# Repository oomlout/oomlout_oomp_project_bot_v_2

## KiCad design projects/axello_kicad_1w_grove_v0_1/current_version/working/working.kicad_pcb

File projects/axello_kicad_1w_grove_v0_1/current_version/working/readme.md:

# kicad
 
## summary 
* id: axello_kicad_1w_grove_v0_1
* user: axello
* name: kicad
* board: 1w_grove_v0_1
* repo: https://github.com/axello/kicad
* src_file_repo_kicad_pcb: 6.0/projects/1w-grove-v0.1/1w-grove-v0.1.kicad_pcb
* src_file_repo_kicad_pcb_link: https://github.com/axello/kicad/tree/master/6.0/projects/1w-grove-v0.1/1w-grove-v0.1.kicad_pcb
* src_file_repo_kicad_sch: 6.0/projects/1w-grove-v0.1/1w-grove-v0.1.kicad_sch
* src_file_repo_kicad_sch_link: https://github.com/axello/kicad/tree/master/6.0/projects/1w-grove-v0.1/1w-grove-v0.1.kicad_sch

* src_file_repo_sch: 6.0/projects/1w-grove-v0.1/1w-grove-v0.1.sch
* src_file_repo_sch_link: https://github.com/axello/kicad/tree/master/6.0/projects/1w-grove-v0.1/1w-grove-v0.1.sch
* full details link: https://github.com/oomlout/oomlout_oomp_project_bot_v_2/tree/main/projects/axello_kicad_1w_grove_v0_1/current_version/working  

## pcb  

[board (pdf)](working.pdf)  

## working_bom
| Id | Designator | Footprint | Quantity | Designation | Supplier and ref |  | None | 
| --- | --- | --- | --- | --- | --- | --- | --- | 
| 1 | U4,U6,U10,U11 | schroef_3.5mm | 4 | schroef_3.5mm |  |  | [''] | 
| 2 | C1 | C_0805_2012Metric | 1 | 100pF |  |  | [''] | 
| 3 | C2 | C_0805_2012Metric | 1 | 100nF |  |  | [''] | 
| 4 | Q1 | SOT-323 | 1 | BSS138BKW |  |  | [''] | 
| 5 | Q2 | SOT-23-3 | 1 | NX2301P |  |  | [''] | 
| 6 | R1,R2,R7 | R_0805_2012Metric | 3 | 10k |  |  | [''] | 
| 7 | R4 | R_0805_2012Metric | 1 | 5.6k |  |  | [''] | 
| 8 | R5,R6,R8 | R_0805_2012Metric | 3 | 22R |  |  | [''] | 
| 9 | CN2,CN3,CN4,CN1,CN5 | rj10-v2 | 5 | RJ10 |  |  | [''] | 
| 10 | F1 | C1210 | 1 | Polyfuse_Small |  |  | [''] | 
| 11 | CN6 | grove-v0.1 | 1 | grove |  |  | [''] | 
| 12 | U3 | CE-140 | 1 | CE-mark |  |  | [''] |

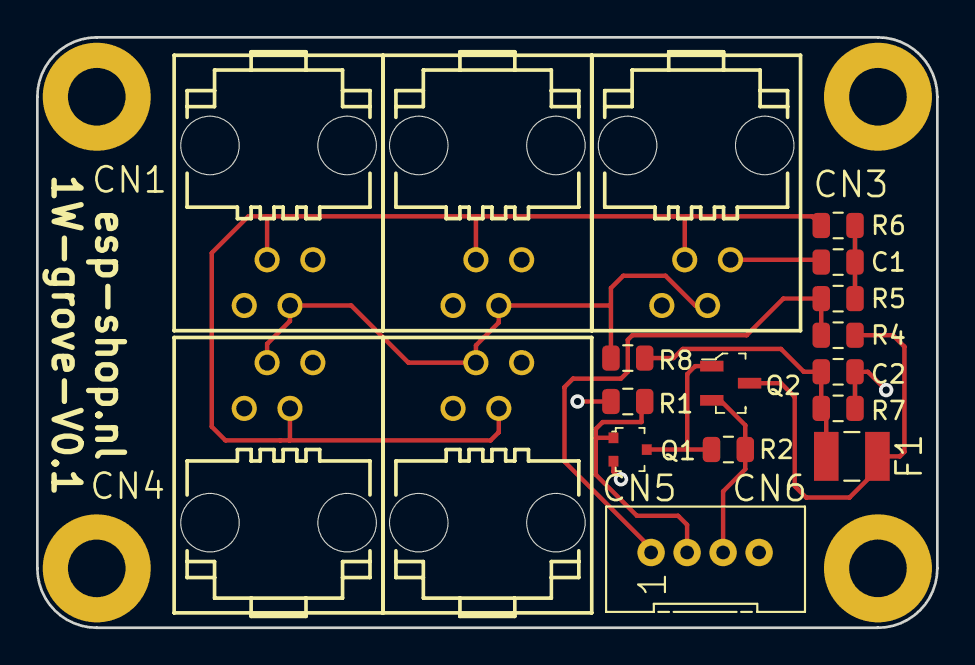
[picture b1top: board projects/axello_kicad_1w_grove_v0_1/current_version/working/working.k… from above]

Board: 2 copper layers, 50.0 x 32.8 mm, 23 parts (1 on the bottom side), 10 nets.

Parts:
C1: 100pF; C_0805_2012Metric
C2: 100nF; C_0805_2012Metric
CN1, CN2, CN3, CN4, CN5: RJ10; rj10-v2
CN6: grove; grove-v0.1
F1: Polyfuse_Small; C1210
Q1: BSS138BKW; SOT-323
Q2: NX2301P; SOT-23-3
R1, R2, R7: 10k; R_0805_2012Metric
R4: 5.6k; R_0805_2012Metric
R5, R6, R8: 22R; R_0805_2012Metric
U3: CE-mark; CE-140
U4, U6, U10, U11: schroef_3.5mm

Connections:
unnamed: C1.1, R5.2, R6.1
unnamed: C1.2, C2.2, CN1.1, CN2.1, CN3.1, CN4.1, CN5.1, CN6.4, Q1.2 (S), R1.1, R7.1
unnamed: C2.1, F1.1, R7.2, R8.1
unnamed: CN1.2, CN2.2, CN3.2, CN4.2, CN5.2, R8.2
unnamed: CN1.3, CN2.3, CN3.3, CN4.3, CN5.3, R6.2
unnamed: F1.2, Q2.3 (D), R4.2
unnamed: CN6.2, Q1.1 (G), R1.2
unnamed: Q1.3 (D), Q2.1 (G), R2.1
unnamed: CN6.3, Q2.2 (S), R2.2
unnamed: CN6.1, R4.1, R5.1

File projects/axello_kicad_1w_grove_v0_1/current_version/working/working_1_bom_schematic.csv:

"Source:","C:\gh\oomlout_oomp_project_bot_v_2\projects\axello_kicad_1w_grove_v0_1\current_version\working\working_1.kicad_sch"
"Date:","26/09/2023 20:39:30"
"Tool:","Eeschema 7.0.6"
"Generator:","C:/Program Files/KiCad/7.0/bin/scripting/plugins/bom_csv_grouped_by_value_with_fp.py"
"Component Count:","26"
"Ref","Qnty","Value","Cmp name","Footprint","Description","Vendor","DNP"
"C1","1","100pF","Device_C","1wire-v0.4:C_0805_2012Metric","","",""
"C2","1","100nF","Device_C","1wire-v0.4:C_0805_2012Metric","","",""
"CN1, CN2, CN3, CN4, CN5","5","RJ10","RJ10","1w-esp32-v0.4:rj10-v2","","",""
"CN6","1","grove","RJ10","grove:grove-v0.1","","",""
"F1","1","Polyfuse_Small","Polyfuse_Small","1wire-v0.4:C1210","","",""
"FID1, FID2, FID3","3","Fiducial","Fiducial","1w-esp32-v0.4:Fiducial_1mm_Mask3mm","","",""
"Q1","1","BSS138BKW","Device_Q_NMOS_GSD","1wire-v0.4:SOT-323","","",""
"Q2","1","NX2301P","Device_Q_PMOS_GSD","1wire-v0.4:SOT-23-3","","",""
"R1, R2, R7","3","10k","Device_R_Small","1wire-v0.4:R_0805_2012Metric","","",""
"R4","1","5.6k","Device_R_Small","1wire-v0.4:R_0805_2012Metric","","",""
"R5, R6, R8","3","22R","Device_R_Small","1wire-v0.4:R_0805_2012Metric","","",""
"U3","1","CE-mark","CE-mark","1w-esp32-v0.4:CE-140","","",""
"U4, U6, U10, U11","4","schroef_3.5mm","schroef_3.5mm","1w-esp32-v0.4:schroef_3.5mm","","",""

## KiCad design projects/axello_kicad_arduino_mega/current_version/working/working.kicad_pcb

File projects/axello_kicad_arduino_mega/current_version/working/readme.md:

# kicad
 
## summary 
* id: axello_kicad_arduino_mega
* user: axello
* name: kicad
* board: arduino_mega
* repo: https://github.com/axello/kicad
* src_file_repo_kicad_pcb: Arduino_Mega_433Mhz_Shield/Arduino_Mega.kicad_pcb
* src_file_repo_kicad_pcb_link: https://github.com/axello/kicad/tree/master/Arduino_Mega_433Mhz_Shield/Arduino_Mega.kicad_pcb
* src_file_repo_kicad_sch: 6.0/projects/NodeMCU-Metriful2/NodeMCU-Metriful.kicad_sch
* src_file_repo_kicad_sch_link: https://github.com/axello/kicad/tree/master/6.0/projects/NodeMCU-Metriful2/NodeMCU-Metriful.kicad_sch

* src_file_repo_sch: Arduino_Mega_433Mhz_Shield/Arduino_Mega.sch
* src_file_repo_sch_link: https://github.com/axello/kicad/tree/master/Arduino_Mega_433Mhz_Shield/Arduino_Mega.sch
* full details link: https://github.com/oomlout/oomlout_oomp_project_bot_v_2/tree/main/projects/axello_kicad_arduino_mega/current_version/working  

## schematic  
  
[schematic (pdf)](working_schematic.pdf) 

## pcb  

[board (pdf)](working.pdf)  

## working_bom
| Id | Designator | Footprint | Quantity | Designation | Supplier and ref |  | None | 
| --- | --- | --- | --- | --- | --- | --- | --- | 
| 1 | P9,P10,P13 | Arduino_1pin | 3 | CONN_01X01 |  |  | [''] | 
| 2 | J1 | Power_Strip_Arduino_Mega_2x18 | 1 | Arduino Mega POWER |  |  | [''] | 
| 3 | P1 | Socket_Strip_Arduino_1x08 | 1 | Communication |  |  | [''] | 
| 4 | AE1 | Pin_Header_Straight_1x01 | 1 | Tx Antenna |  |  | [''] | 
| 5 | AE2 | Pin_Header_Straight_1x01 | 1 | Rx Antenna |  |  | [''] | 
| 6 | U1 | RCV | 1 | RXB6_RCV |  |  | [''] | 
| 7 | U2 | XMIT | 1 | RXB6_XMIT |  |  | [''] | 
| 8 | C1 | C_Rect_L9.0mm_W2.5mm_P7.50mm_MKT | 1 | 100n |  |  | [''] | 
| 9 | C2 | CP_Radial_D5.0mm_P2.00mm | 1 | 0.47Âµ |  |  | [''] | 
| 10 | C3 | CP_Radial_D5.0mm_P2.00mm | 1 | 10ÂµF |  |  | [''] | 
| 11 | JP1 | Pin_Header_Straight_1x02_Pitch1.27mm | 1 | RF_GND |  |  | [''] | 
| 12 | G*** | LOGO2 | 1 | LOGO |  |  | [''] | 

## bom_schematic
| Ref | Qnty | Value | Cmp name | Footprint | Description | Vendor | DNP | 
| --- | --- | --- | --- | --- | --- | --- | --- | 
| AE1, AE2 | 2 | Antenna | Antenna | Pin_Headers:Pin_Header_Straight_1x01 |  |  |  | 
| C1 | 1 | 100n | C_Small | Capacitors_THT:C_Rect_L9.0mm_W2.5mm_P7.50mm_MKT |  |  |  | 
| C2 | 1 | 0.47Âµ | CP | Capacitors_THT:CP_Radial_D5.0mm_P2.00mm |  |  |  | 
| C3 | 1 | 10ÂµF | CP | Capacitors_THT:CP_Radial_D5.0mm_P2.00mm |  |  |  | 
| J1 | 1 | Arduino_Mega_POWER | ARDUINO_MEGA_POWER | Socket_Arduino_Mega:Power_Strip_Arduino_Mega_2x18 |  |  |  | 
| JP1 | 1 | RF_GND | Jumper_NO_Small | Pin_Headers:Pin_Header_Straight_1x02_Pitch1.27mm |  |  |  | 
| P1 | 1 | Communication | CONN_01X08 | Socket_Arduino_Mega:Socket_Strip_Arduino_1x08 |  |  |  | 
| U1 | 1 | RXB6_RCV | RXB6_RCV | RF:RCV |  |  |  | 
| U2 | 1 | RXB6_XMIT | RXB6_XMIT | RF:XMIT |  |  |  |

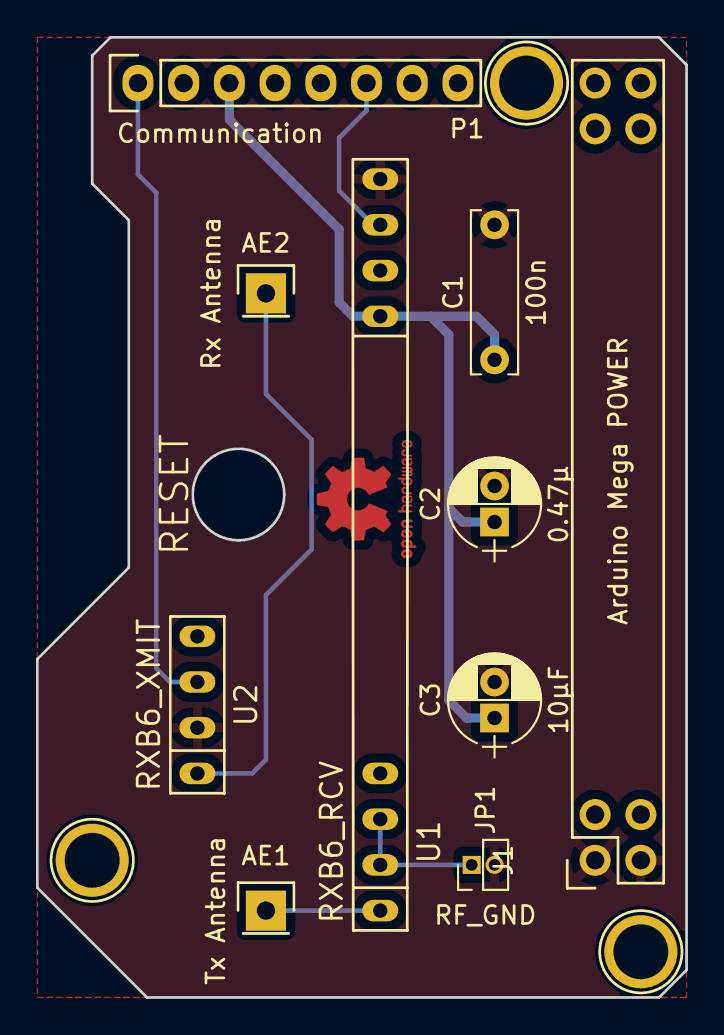
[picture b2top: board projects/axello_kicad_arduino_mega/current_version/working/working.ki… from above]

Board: 2 copper layers, 36.1 x 53.3 mm, 13 parts (0 on the bottom side), 8 nets.

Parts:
AE1: Tx Antenna; Pin_Header_Straight_1x01
AE2: Rx Antenna; Pin_Header_Straight_1x01
C1: 100n; C_Rect_L9.0mm_W2.5mm_P7.50mm_MKT
C2: 0.47µ; CP_Radial_D5.0mm_P2.00mm
C3: 10µF; CP_Radial_D5.0mm_P2.00mm
J1: Arduino Mega POWER; Power_Strip_Arduino_Mega_2x18
JP1: RF_GND; Pin_Header_Straight_1x02_Pitch1.27mm
P1: Communication; Socket_Strip_Arduino_1x08
P9, P10, P13: CONN_01X01; Arduino_1pin
U1: RXB6_RCV; RCV
U2: RXB6_XMIT; XMIT

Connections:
+5V: J1.35, J1.36, U2.4
/14(Tx3): P1.1, U2.3
/16(Tx2): C1.1, C2.1, C3.1, P1.3, U1.5
/19(Rx1): P1.6, U1.7
GND: C1.2, C2.2, C3.2, J1.1, J1.2, JP1.2, U1.8, U2.2
unnamed: AE1.1, U1.1
unnamed: AE2.1, U2.1
unnamed: JP1.1, U1.2, U1.3

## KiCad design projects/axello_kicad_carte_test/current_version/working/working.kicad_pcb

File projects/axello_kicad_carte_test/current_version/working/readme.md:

# kicad
 
## summary 
* id: axello_kicad_carte_test
* user: axello
* name: kicad
* board: carte_test
* repo: https://github.com/axello/kicad
* src_file_repo_kicad_pcb: demos/test_xil_95108/carte_test.kicad_pcb
* src_file_repo_kicad_pcb_link: https://github.com/axello/kicad/tree/master/demos/test_xil_95108/carte_test.kicad_pcb
* src_file_repo_kicad_sch: demos/test_xil_95108/carte_test.kicad_sch
* src_file_repo_kicad_sch_link: https://github.com/axello/kicad/tree/master/demos/test_xil_95108/carte_test.kicad_sch

* src_file_repo_sch: Arduino_Mega_433Mhz_Shield/Arduino_Mega.sch
* src_file_repo_sch_link: https://github.com/axello/kicad/tree/master/Arduino_Mega_433Mhz_Shield/Arduino_Mega.sch
* full details link: https://github.com/oomlout/oomlout_oomp_project_bot_v_2/tree/main/projects/axello_kicad_carte_test/current_version/working  

## schematic  
  
[schematic (pdf)](working_schematic.pdf) 

## pcb  

[board (pdf)](working.pdf)  

## working_bom
| Id | Designator | Footprint | Quantity | Designation | Supplier and ref |  | None | 
| --- | --- | --- | --- | --- | --- | --- | --- | 
| 1 | D1,D4 | D_DO-35_SOD27_P12.70mm_Horizontal | 2 | 1N4004 |  |  | [''] | 
| 2 | SW1,SW2 | SW_PUSH_6mm_h4.3mm | 2 | SW_PUSH |  |  | [''] | 
| 3 | U2 | PLCC84 | 1 | XC95108PC84 |  |  | [''] | 
| 4 | U4 | DIP-14_W7.62mm_LongPads | 1 | 74HC04 |  |  | [''] | 
| 5 | P4 | PinHeader_2x02_P2.54mm_Vertical | 1 | CONN_2X2 |  |  | [''] | 
| 6 | K1 | PinHeader_1x03_P2.54mm_Vertical | 1 | CONN_3 |  |  | [''] | 
| 7 | R2,R3 | R_Axial_DIN0207_L6.3mm_D2.5mm_P10.16mm_Horizontal | 2 | 330 |  |  | [''] | 
| 8 | R8,R9 | R_Axial_DIN0207_L6.3mm_D2.5mm_P10.16mm_Horizontal | 2 | 2,2K |  |  | [''] | 
| 9 | R10 | R_Axial_DIN0207_L6.3mm_D2.5mm_P10.16mm_Horizontal | 1 | 75 |  |  | [''] | 
| 10 | R1 | R_Axial_DIN0207_L6.3mm_D2.5mm_P10.16mm_Horizontal | 1 | 100K |  |  | [''] | 
| 11 | R5,R4 | R_Axial_DIN0207_L6.3mm_D2.5mm_P10.16mm_Horizontal | 2 | 4,7K |  |  | [''] | 
| 12 | R6 | R_Axial_DIN0207_L6.3mm_D2.5mm_P10.16mm_Horizontal | 1 | 1,1k |  |  | [''] | 
| 13 | U1 | DIP-16_W7.62mm_Socket_LongPads | 1 | TDA8702 |  |  | [''] | 
| 14 | X1 | Crystal_HC18-U_Horizontal | 1 | 10MHz |  |  | [''] | 
| 15 | R7 | R_Axial_DIN0207_L6.3mm_D2.5mm_P10.16mm_Horizontal | 1 | 1,1K |  |  | [''] | 
| 16 | D3,D2 | LED_D5.0mm | 2 | LED |  |  | [''] | 
| 17 | U6 | DIP-8_W7.62mm_LongPads | 1 | LM318N |  |  | [''] | 
| 18 | J1 | DSUB-25_Female_Horizontal_P2.77x2.84mm_EdgePinOffset9.90mm_Housed_MountingHolesOffset11.32mm | 1 | DB25 |  |  | [''] | 
| 19 | U3 | TO-220-3_Horizontal_TabDown | 1 | LM7805 |  |  | [''] | 
| 20 | J2 | DSUB-9_Female_Horizontal_P2.77x2.84mm_EdgePinOffset4.94mm_Housed_MountingHolesOffset7.48mm | 1 | DB9FEM |  |  | [''] | 
| 21 | P2 | TerminalBlock_Phoenix_MKDS-1,5-3-5.08_1x03_P5.08mm_Horizontal | 1 | CONN_3 |  |  | [''] | 
| 22 | P3 | TerminalBlock_Phoenix_MKDS-1,5-2-5.08_1x02_P5.08mm_Horizontal | 1 | CONN_2 |  |  | [''] | 
| 23 | C13,C3,C2,C14 | CP_Axial_L10.0mm_D4.5mm_P15.00mm_Horizontal | 4 | 10uF |  |  | [''] | 
| 24 | C6 | CP_Axial_L10.0mm_D4.5mm_P15.00mm_Horizontal | 1 | 47uF |  |  | [''] | 
| 25 | U5 | DIP-28__300__600_ELL | 1 | RAM_32KO |  |  | [''] | 
| 26 | C1,C12 | C_1206 | 2 | 100nF |  |  | [''] | 
| 27 | C4,C5 | C_1206 | 2 | 22pF |  |  | [''] | 
| 28 | C11,C10,C8,C7 | C_1206_3216Metric_Pad1.24x1.80mm_HandSolder | 4 | 100nF |  |  | [''] | 

## bom_schematic
| Ref | Qnty | Value | Cmp name | Footprint | Description | Vendor | DNP | 
| --- | --- | --- | --- | --- | --- | --- | --- | 
| C1, C12 | 2 | 100nF | C | Capacitors_SMD:C_1206 | Unpolarized capacitor |  |  | 
| C2, C3, C13, C14 | 4 | 10uF | CP | Capacitor_THT:CP_Axial_L10.0mm_D4.5mm_P15.00mm_Horizontal | Polarised capacitor |  |  | 
| C4, C5 | 2 | 22pF | C | Capacitors_SMD:C_1206 | Unpolarized capacitor |  |  | 
| C6 | 1 | 47uF | CP | Capacitor_THT:CP_Axial_L10.0mm_D4.5mm_P15.00mm_Horizontal | Polarised capacitor |  |  | 
| C7, C8, C10, C11 | 4 | 100nF | C | Capacitor_SMD:C_1206_3216Metric_Pad1.24x1.80mm_HandSolder | Unpolarized capacitor |  |  | 
| D1, D4 | 2 | 1N4004 | DIODE | Diode_THT:D_DO-35_SOD27_P12.70mm_Horizontal |  |  |  | 
| D2, D3 | 2 | LED | LED | LED_THT:LED_D5.0mm |  |  |  | 
| J1 | 1 | DB25 | DB25 | Connector_Dsub:DSUB-25_Female_Horizontal_P2.77x2.84mm_EdgePinOffset9.90mm_Housed_MountingHolesOffset11.32mm |  |  |  | 
| J2 | 1 | DB9FEM | DB9 | Connector_Dsub:DSUB-9_Female_Horizontal_P2.77x2.84mm_EdgePinOffset4.94mm_Housed_MountingHolesOffset7.48mm |  |  |  | 
| K1 | 1 | CONN_3 | CONN_3 | Connector_PinHeader_2.54mm:PinHeader_1x03_P2.54mm_Vertical |  |  |  | 
| P2 | 1 | CONN_3 | CONN_3 | TerminalBlock_Phoenix:TerminalBlock_Phoenix_MKDS-1,5-3-5.08_1x03_P5.08mm_Horizontal |  |  |  | 
| P3 | 1 | CONN_2 | CONN_2 | TerminalBlock_Phoenix:TerminalBlock_Phoenix_MKDS-1,5-2-5.08_1x02_P5.08mm_Horizontal |  |  |  | 
| P4 | 1 | CONN_2X2 | CONN_2X2 | Connector_PinHeader_2.54mm:PinHeader_2x02_P2.54mm_Vertical |  |  |  | 
| R1 | 1 | 100K | R | Resistor_THT:R_Axial_DIN0207_L6.3mm_D2.5mm_P10.16mm_Horizontal | Resistor |  |  | 
| R2, R3 | 2 | 330 | R | Resistor_THT:R_Axial_DIN0207_L6.3mm_D2.5mm_P10.16mm_Horizontal | Resistor |  |  | 
| R4, R5 | 2 | 4,7K | R | Resistor_THT:R_Axial_DIN0207_L6.3mm_D2.5mm_P10.16mm_Horizontal | Resistor |  |  | 
| R6 | 1 | 1,1k | R | Resistor_THT:R_Axial_DIN0207_L6.3mm_D2.5mm_P10.16mm_Horizontal | Resistor |  |  | 
| R7 | 1 | 1,1K | R | Resistor_THT:R_Axial_DIN0207_L6.3mm_D2.5mm_P10.16mm_Horizontal | Resistor |  |  | 
| R8, R9 | 2 | 2,2K | R | Resistor_THT:R_Axial_DIN0207_L6.3mm_D2.5mm_P10.16mm_Horizontal | Resistor |  |  | 
| R10 | 1 | 75 | R | Resistor_THT:R_Axial_DIN0207_L6.3mm_D2.5mm_P10.16mm_Horizontal | Resistor |  |  | 
| SW1, SW2 | 2 | SW_PUSH | SW_PUSH | Button_Switch_THT:SW_PUSH_6mm_h4.3mm |  |  |  | 
| U1 | 1 | TDA8702 | TDA8702 | Package_DIP:DIP-16_W7.62mm_Socket_LongPads |  |  |  | 
| U2 | 1 | XC95108PC84 | XC95108PC84 | Sockets:PLCC84 |  |  |  | 
| U3 | 1 | LM7805 | LM7805 | Package_TO_SOT_THT:TO-220-3_Horizontal_TabDown |  |  |  | 
| U4 | 1 | 74HC04 | 74HC04 | Package_DIP:DIP-14_W7.62mm_LongPads |  |  |  | 
| U5 | 1 | RAM_32KO | RAM_32KO | Sockets_DIP:DIP-28__300__600_ELL |  |  |  | 
| U6 | 1 | LM318N | LM318N | Package_DIP:DIP-8_W7.62mm_LongPads |  |  |  | 
| X1 | 1 | 10MHz | CRYSTAL | Crystal:Crystal_HC18-U_Horizontal |  |  |  | 

## mounting_holes
| x | y | package | value | ref | size | 
| --- | --- | --- | --- | --- | --- | 
| 0.0 | 25.78 | DSUB-25_Female_Horizontal_P2.77x2.84mm_EdgePinOffset9.90mm_Housed_MountingHolesOffset11.32mm | DB25 | J1 | m3 | 
| 57.79 | 0.0 | DSUB-9_Female_Horizontal_P2.77x2.84mm_EdgePinOffset4.94mm_Housed_MountingHolesOffset7.48mm | DB9FEM | J2 | m3 |

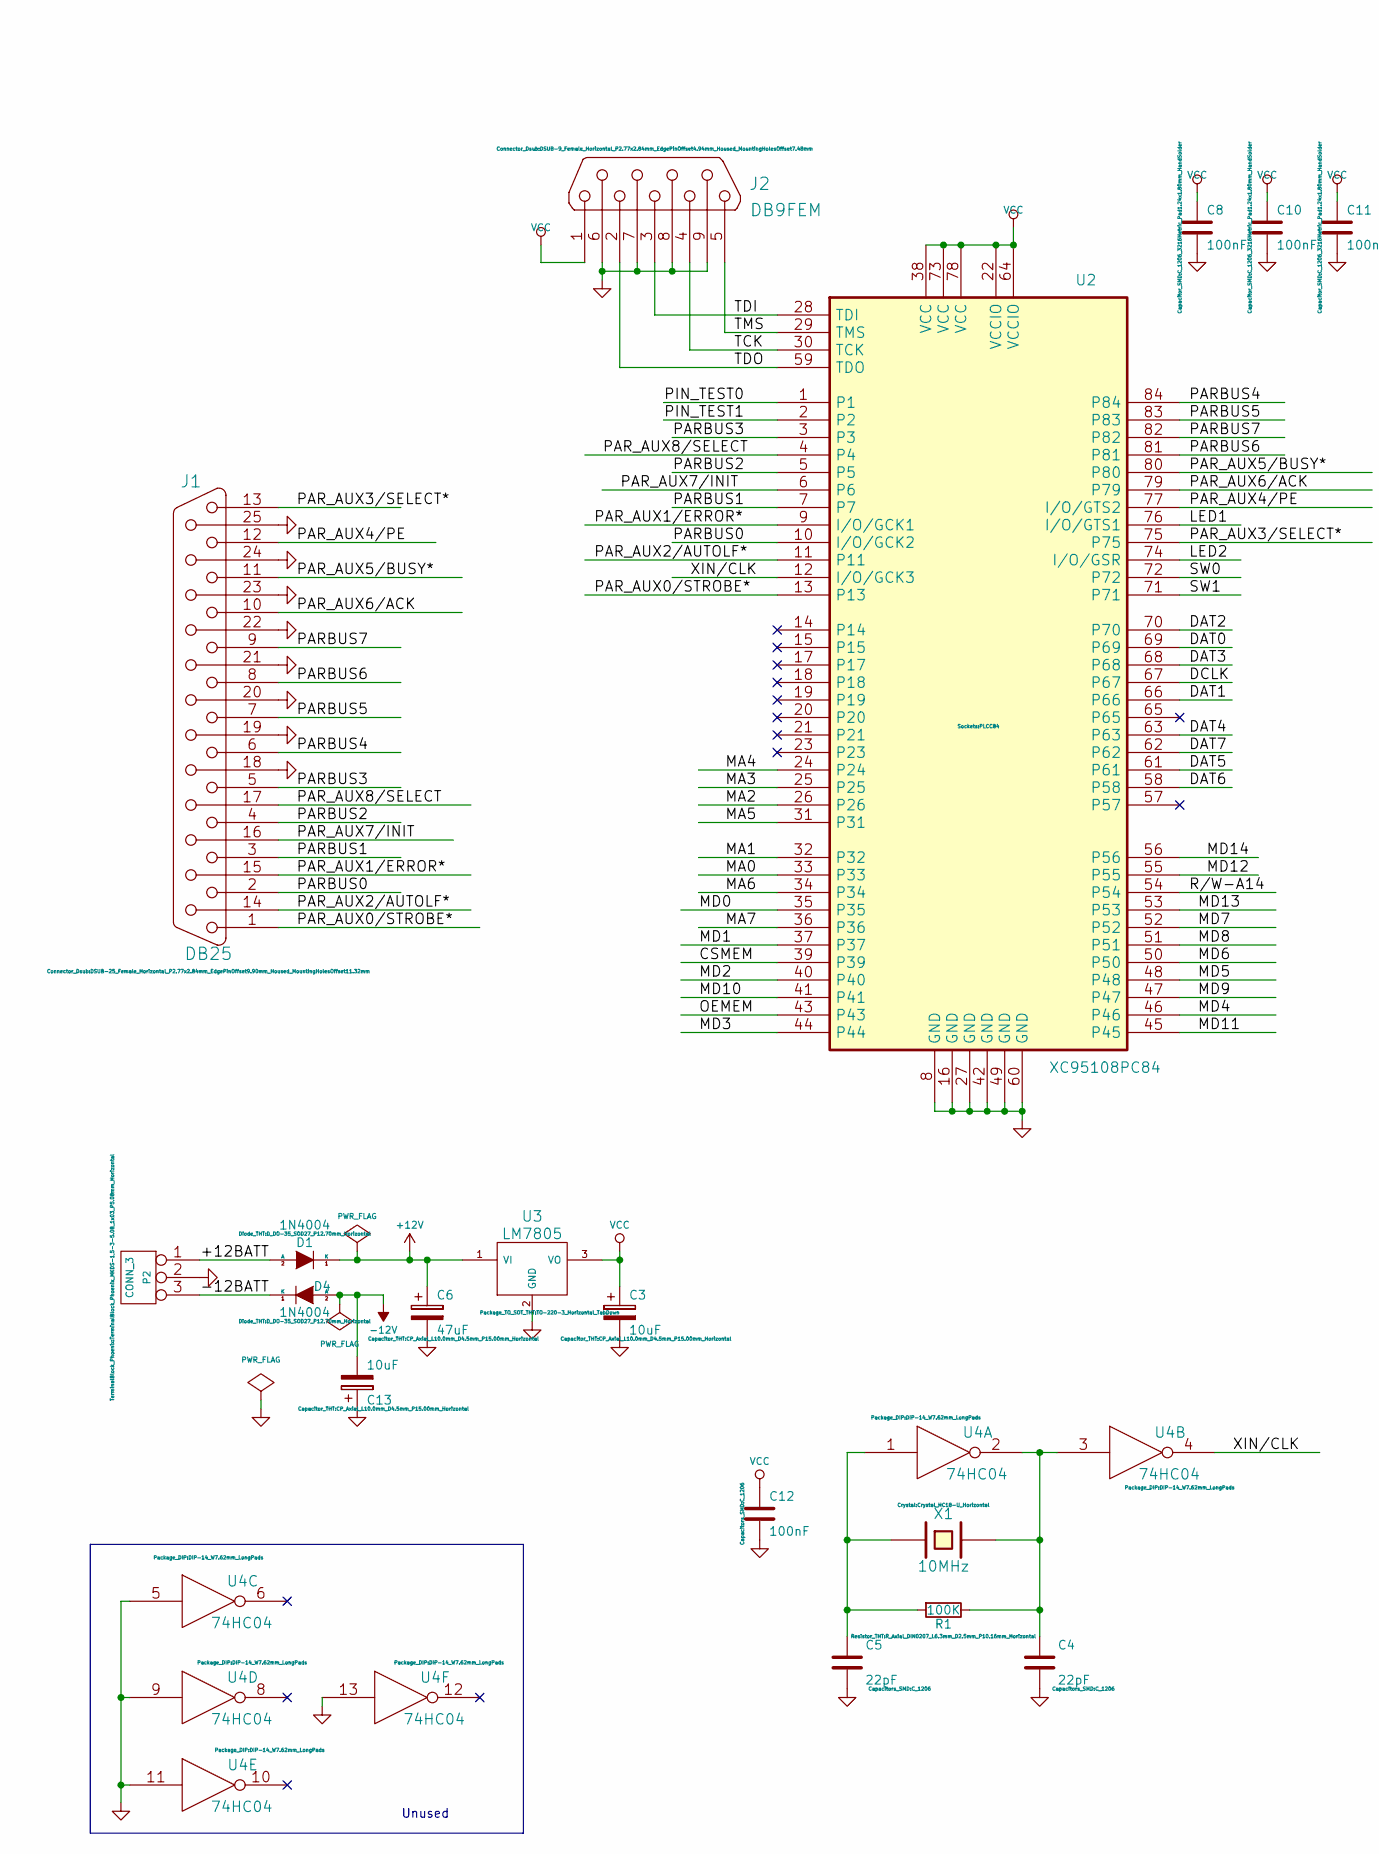
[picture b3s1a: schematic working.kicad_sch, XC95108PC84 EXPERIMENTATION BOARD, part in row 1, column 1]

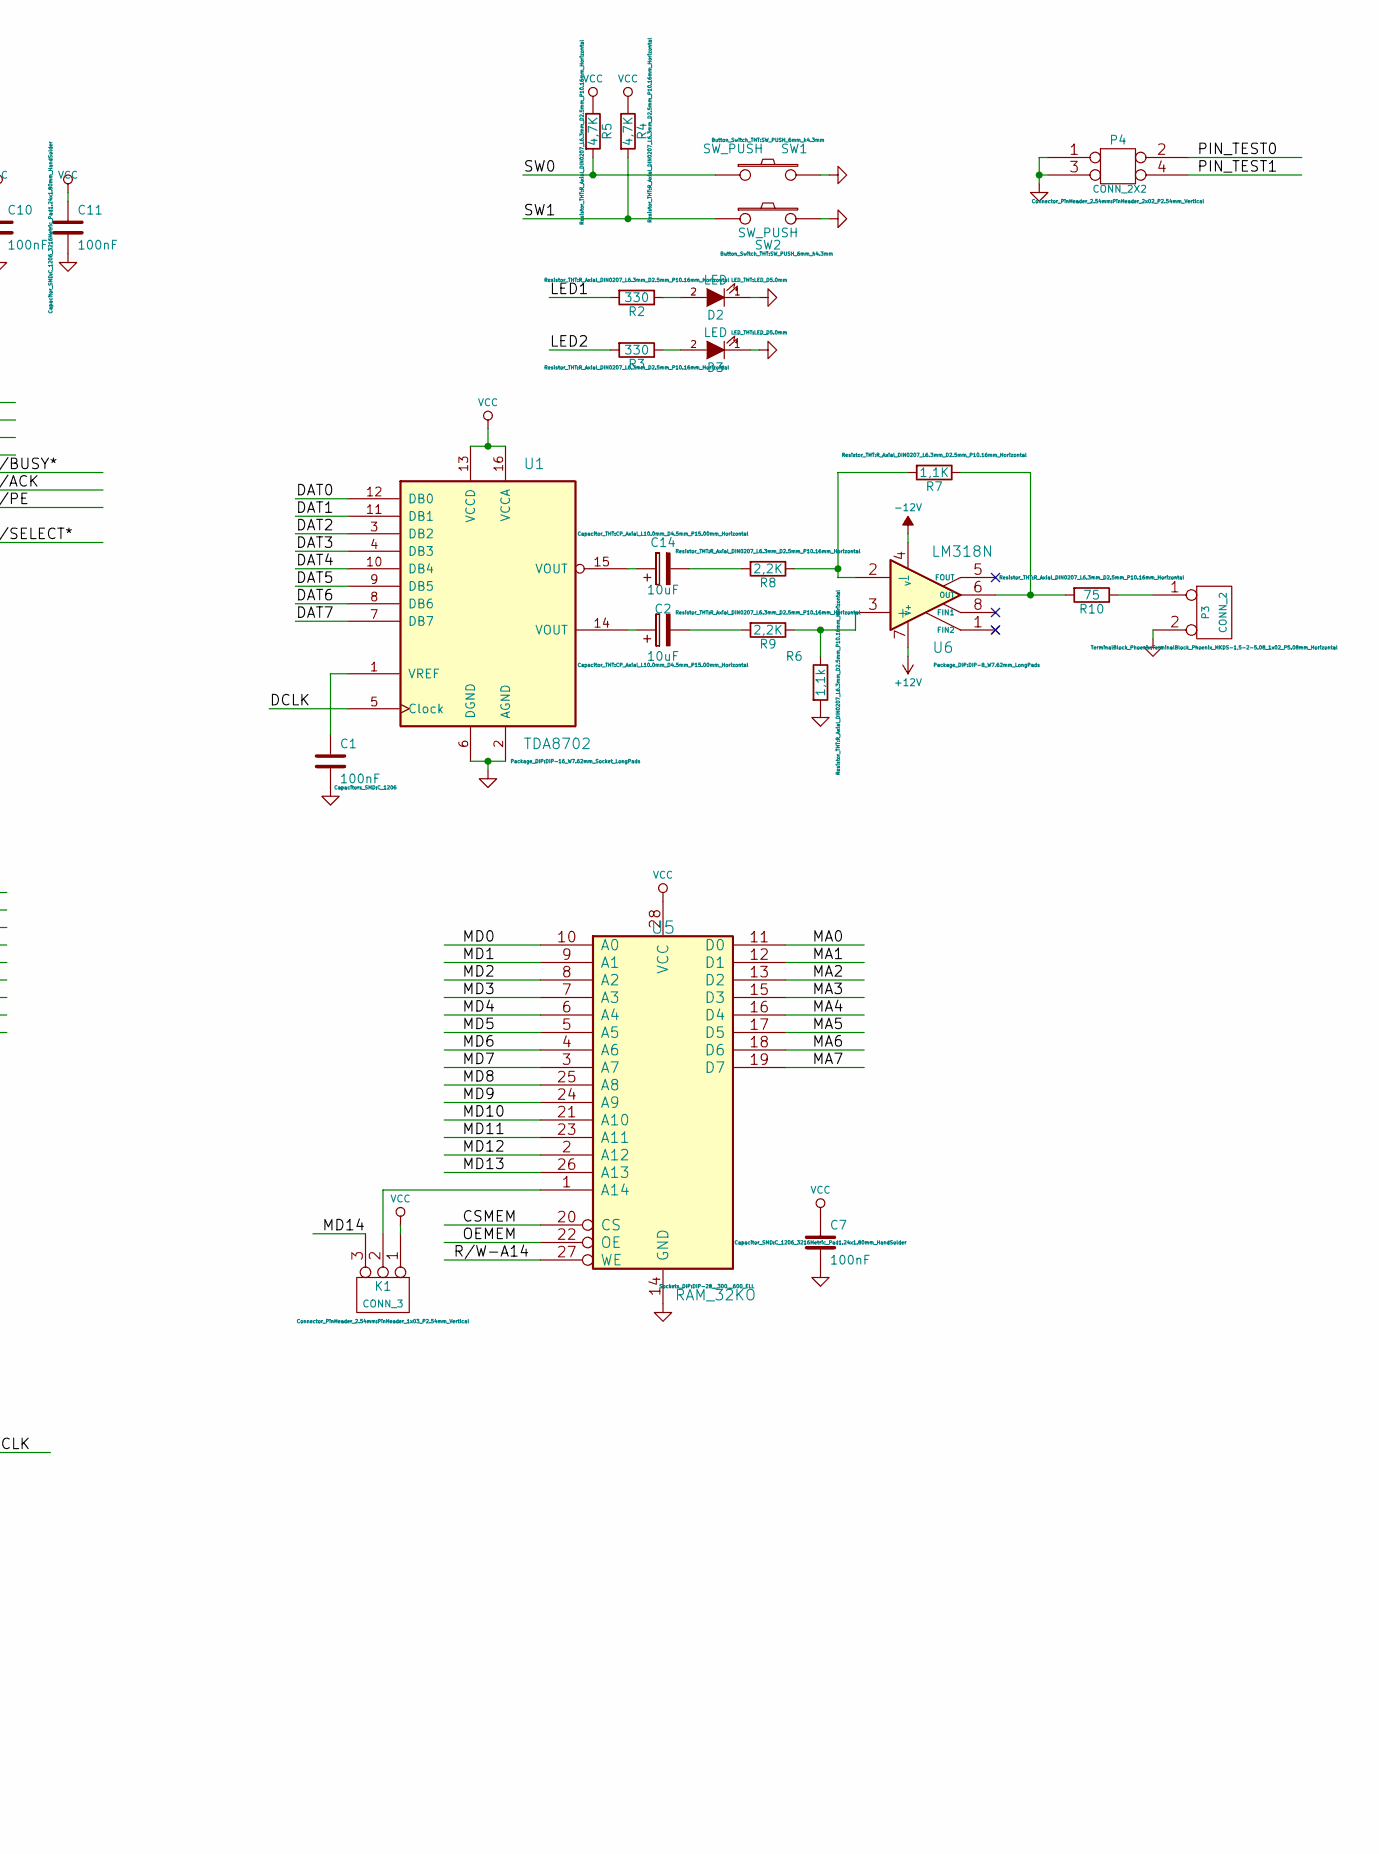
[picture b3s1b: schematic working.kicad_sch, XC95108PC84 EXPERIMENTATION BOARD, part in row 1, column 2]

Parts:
C1, C12: 100nF; C_1206
C2, C3, C13, C14: 10uF; CP_Axial_L10.0mm_D4.5mm_P15.00mm_Horizontal
C4, C5: 22pF; C_1206
C6: 47uF; CP_Axial_L10.0mm_D4.5mm_P15.00mm_Horizontal
C7, C8, C10, C11: 100nF; C_1206_3216Metric_Pad1.24x1.80mm_HandSolder
D1, D4: 1N4004; D_DO-35_SOD27_P12.70mm_Horizontal
D2, D3: LED; LED_D5.0mm
J1: DB25; DSUB-25_Female_Horizontal_P2.77x2.84mm_EdgePinOffset9.90mm_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
J2: DB9FEM; DSUB-9_Female_Horizontal_P2.77x2.84mm_EdgePinOffset4.94mm_H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
K1: CONN_3; PinHeader_1x03_P2.54mm_Vertical
P2: CONN_3; TerminalBlock_Phoenix_MKDS-1,5-3-5.08_1x03_P5.08mm_Horizont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
P3: CONN_2; TerminalBlock_Phoenix_MKDS-1,5-2-5.08_1x02_P5.08mm_Horizont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
P4: CONN_2X2; PinHeader_2x02_P2.54mm_Vertical
R1: 100K; R_Axial_DIN0207_L6.3mm_D2.5mm_P10.16mm_Horizontal
R2, R3: 330; R_Axial_DIN0207_L6.3mm_D2.5mm_P10.16mm_Horizontal
R4, R5: 4,7K; R_Axial_DIN0207_L6.3mm_D2.5mm_P10.16mm_Horizontal
R6: 1,1k; R_Axial_DIN0207_L6.3mm_D2.5mm_P10.16mm_Horizontal
R7: 1,1K; R_Axial_DIN0207_L6.3mm_D2.5mm_P10.16mm_Horizontal
R8, R9: 2,2K; R_Axial_DIN0207_L6.3mm_D2.5mm_P10.16mm_Horizontal
R10: 75; R_Axial_DIN0207_L6.3mm_D2.5mm_P10.16mm_Horizontal
SW1, SW2: SW_PUSH; SW_PUSH_6mm_h4.3mm
U1: TDA8702; DIP-16_W7.62mm_Socket_LongPads
U2: XC95108PC84; PLCC84
U3: LM7805; TO-220-3_Horizontal_TabDown
U4: 74HC04; DIP-14_W7.62mm_LongPads
U5: RAM_32KO; DIP-28__300__600_ELL
U6: LM318N; DIP-8_W7.62mm_LongPads
X1: 10MHz; Crystal_HC18-U_Horizontal

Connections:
+12V: C6.1, D1.1 (K), U3.1 (VI), U6.7 (V+)
-12V: C13.2, D4.2 (A), U6.4 (V-)
/+12BATT: D1.2 (A), P2.1
/-12BATT: D4.1 (K), P2.3
/CSMEM: U2.39, U5.20 (CS)
/DAT0: U1.12 (DB0), U2.69
/DAT1: U1.11 (DB1), U2.66
/DAT2: U1.3 (DB2), U2.70
/DAT3: U1.4 (DB3), U2.68
/DAT4: U1.10 (DB4), U2.63
/DAT5: U1.9 (DB5), U2.61
/DAT6: U1.8 (DB6), U2.58
/DAT7: U1.7 (DB7), U2.62
/DCLK: U1.5 (Clock), U2.67
/LED1: R2.2, U2.76 (I/O/GTS1)
/LED2: R3.2, U2.74 (I/O/GSR)
/MA0: U2.33, U5.11 (D0)
/MA1: U2.32, U5.12 (D1)
/MA2: U2.26, U5.13 (D2)
/MA3: U2.25, U5.15 (D3)
/MA4: U2.24, U5.16 (D4)
/MA5: U2.31, U5.17 (D5)
/MA6: U2.34, U5.18 (D6)
/MA7: U2.36, U5.19 (D7)
/MD0: U2.35, U5.10 (A0)
/MD1: U2.37, U5.9 (A1)
/MD2: U2.40, U5.8 (A2)
/MD3: U2.44, U5.7 (A3)
/MD4: U2.46, U5.6 (A4)
/MD5: U2.48, U5.5 (A5)
/MD6: U2.50, U5.4 (A6)
/MD7: U2.52, U5.3 (A7)
/MD8: U2.51, U5.25 (A8)
/MD9: U2.47, U5.24 (A9)
/MD10: U2.41, U5.21 (A10)
/MD11: U2.45, U5.23 (A11)
/MD12: U2.55, U5.2 (A12)
/MD13: U2.53, U5.26 (A13)
/MD14: K1.3, U2.56
/OEMEM: U2.43, U5.22 (OE)
/PARBUS0: J1.2, U2.10 (I/O/GCK2)
/PARBUS1: J1.3, U2.7
/PARBUS2: J1.4, U2.5
/PARBUS3: J1.5, U2.3
/PARBUS4: J1.6, U2.84
/PARBUS5: J1.7, U2.83
/PARBUS6: J1.8, U2.81
/PARBUS7: J1.9, U2.82
/PAR_AUX0/STROBE*: J1.1, U2.13
/PAR_AUX1/ERROR*: J1.15, U2.9 (I/O/GCK1)
/PAR_AUX2/AUTOLF*: J1.14, U2.11
/PAR_AUX3/SELECT*: J1.13, U2.75
/PAR_AUX4/PE: J1.12, U2.77 (I/O/GTS2)
/PAR_AUX5/BUSY*: J1.11, U2.80
/PAR_AUX6/ACK: J1.10, U2.79
/PAR_AUX7/INIT: J1.16, U2.6
/PAR_AUX8/SELECT: J1.17, U2.4
/PIN_TEST0: P4.2, U2.1
/PIN_TEST1: P4.4, U2.2
/R/W-A14: U2.54, U5.27 (WE)
/SW0: R5.2, SW1.1, U2.72
/SW1: R4.2, SW2.1, U2.71
/TCK: J2.4, U2.30 (TCK)
/TDI: J2.3, U2.28 (TDI)
/TDO: J2.2, U2.59 (TDO)
/TMS: J2.5, U2.29 (TMS)
/XIN/CLK: U2.12 (I/O/GCK3), U4.4
GND: C1.2, C3.2, C4.2, C5.2, C6.2, C7.2, C8.2, C10.2, C11.2, C12.2, C13.1, D2.1 (K), D3.1 (K), J1.18, J1.19, J1.20, J1.21, J1.22, J1.23, J1.24, J1.25, J2.6, J2.7, J2.8, J2.9, P2.2 (PM), P3.2 (PM), P4.1, P4.3, R6.2, SW1.2, SW2.2, U1.2 (AGND), U1.6 (DGND), U2.8 (GND), U2.16 (GND), U2.27 (GND), U2.42 (GND), U2.49 (GND), U2.60 (GND), U3.2 (GND), U4.5, U4.7 (GND), U4.9, U4.11, U4.13, U5.14 (GND)
unnamed: C1.1, U1.1 (VREF)
unnamed: C2.1, U1.14 (VOUT)
unnamed: C2.2, R9.2
unnamed: C4.1, R1.1, U4.2, U4.3, X1.2
unnamed: C5.1, R1.2, U4.1, X1.1
unnamed: C14.1, U1.15 (VOUT)
unnamed: C14.2, R8.2
unnamed: D2.2 (A), R2.1
unnamed: D3.2 (A), R3.1
unnamed: K1.2 (PM), U5.1 (A14)
unnamed: P3.1, R10.1
unnamed: R6.1, R9.1, U6.3 (+)
unnamed: R7.2, R8.1, U6.2 (-)
unnamed: R7.1, R10.2, U6.6 (OUT)
VCC: C3.1, C7.1, C8.1, C10.1, C11.1, C12.1, J2.1, K1.1, R4.1, R5.1, U1.13 (VCCD), U1.16 (VCCA), U2.22 (VCCIO), U2.38 (VCC), U2.64 (VCCIO), U2.73 (VCC), U2.78 (VCC), U3.3 (VO), U4.14 (VCC), U5.28 (VCC)

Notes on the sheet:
Unused

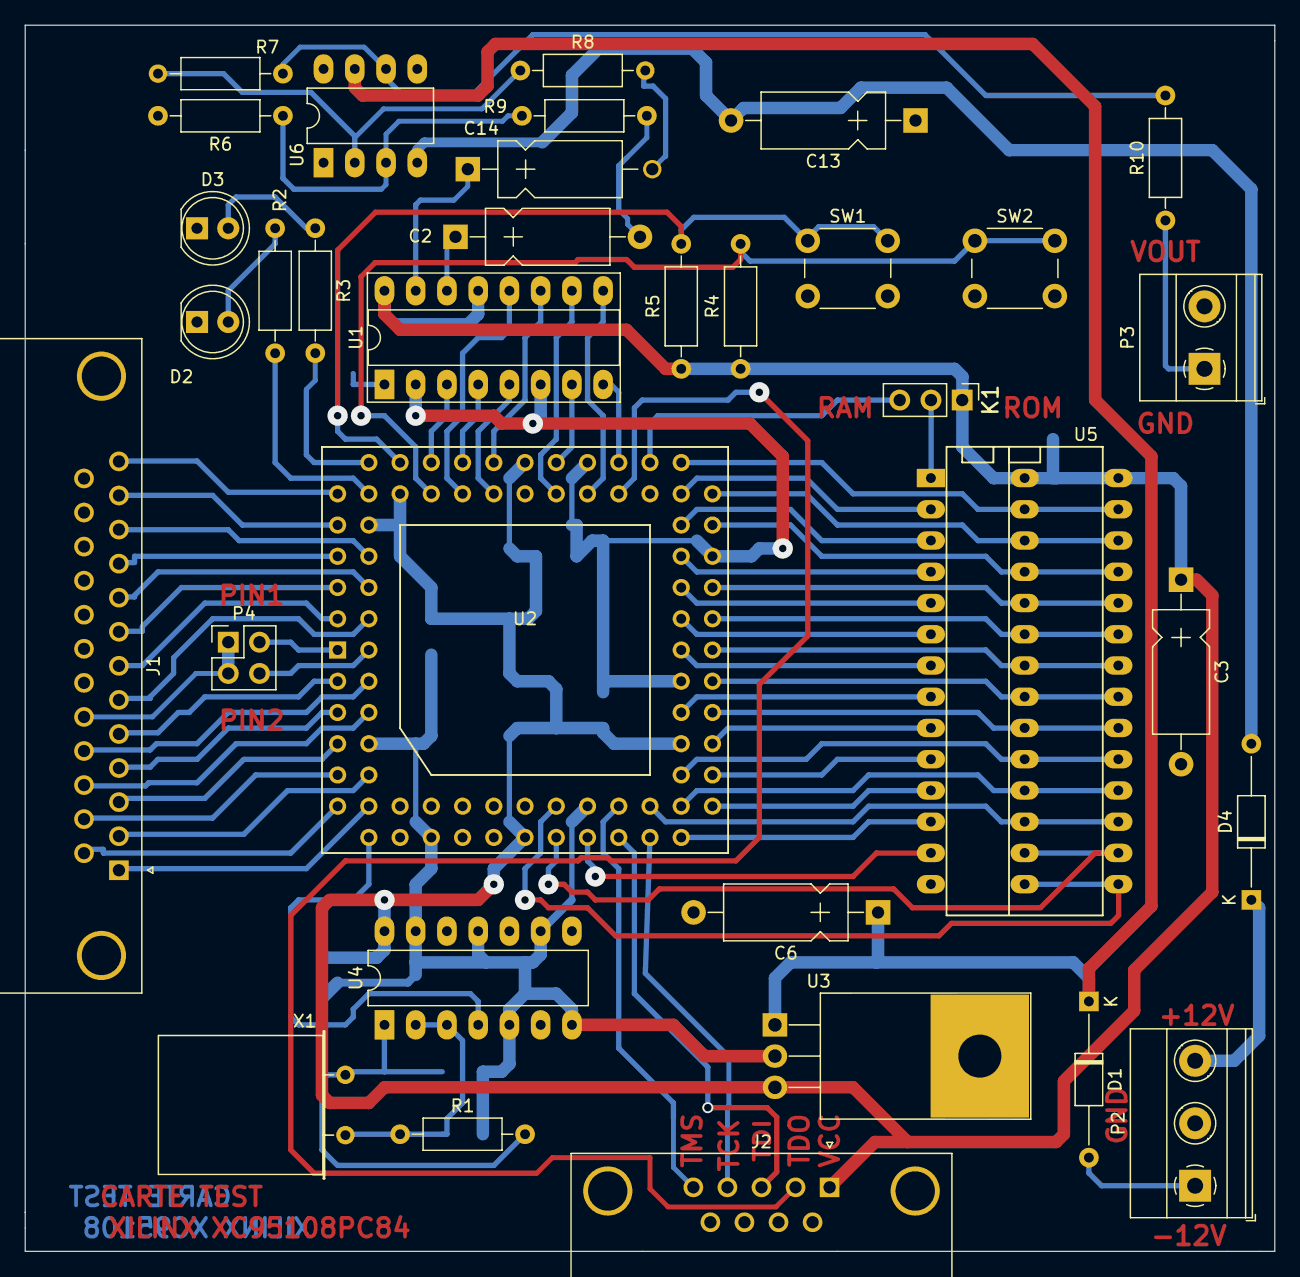
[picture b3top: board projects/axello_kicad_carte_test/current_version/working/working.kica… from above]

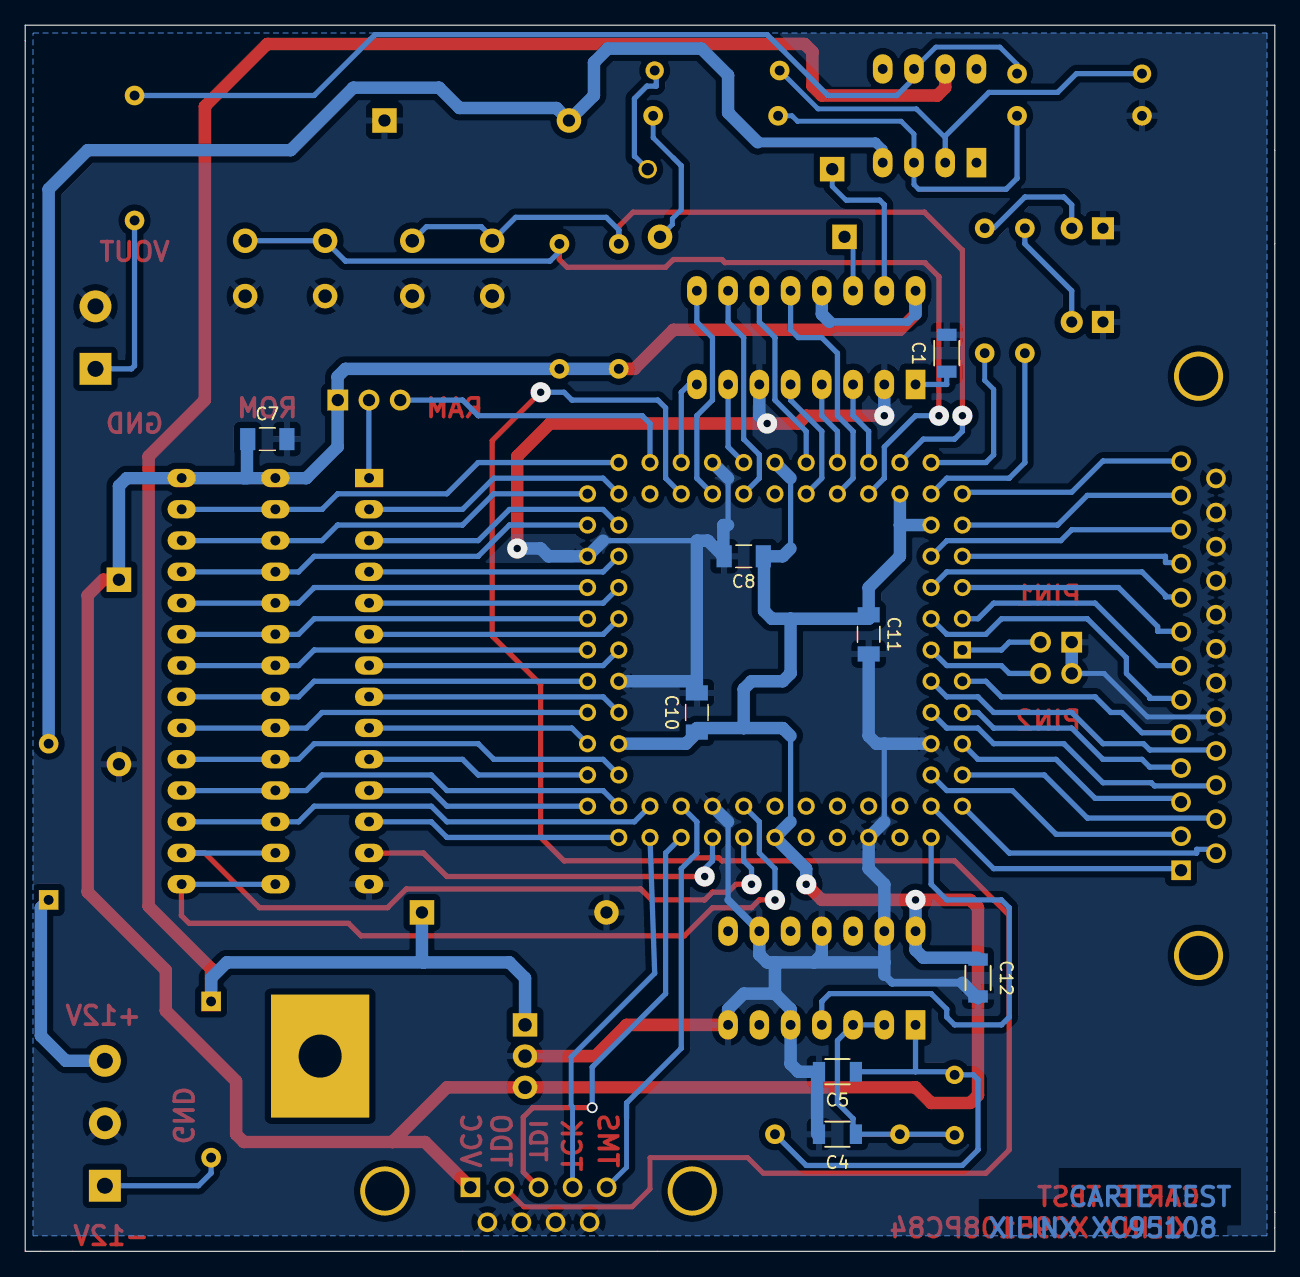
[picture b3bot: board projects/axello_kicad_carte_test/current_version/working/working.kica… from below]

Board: 2 copper layers, 101.6 x 99.7 mm, 42 parts (8 on the bottom side), 83 nets.

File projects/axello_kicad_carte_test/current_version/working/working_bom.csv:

"Id";"Designator";"Footprint";"Quantity";"Designation";"Supplier and ref";
1;"D1,D4";"D_DO-35_SOD27_P12.70mm_Horizontal";2;"1N4004";;;
2;"SW1,SW2";"SW_PUSH_6mm_h4.3mm";2;"SW_PUSH";;;
3;"U2";"PLCC84";1;"XC95108PC84";;;
4;"U4";"DIP-14_W7.62mm_LongPads";1;"74HC04";;;
5;"P4";"PinHeader_2x02_P2.54mm_Vertical";1;"CONN_2X2";;;
6;"K1";"PinHeader_1x03_P2.54mm_Vertical";1;"CONN_3";;;
7;"R2,R3";"R_Axial_DIN0207_L6.3mm_D2.5mm_P10.16mm_Horizontal";2;"330";;;
8;"R8,R9";"R_Axial_DIN0207_L6.3mm_D2.5mm_P10.16mm_Horizontal";2;"2,2K";;;
9;"R10";"R_Axial_DIN0207_L6.3mm_D2.5mm_P10.16mm_Horizontal";1;"75";;;
10;"R1";"R_Axial_DIN0207_L6.3mm_D2.5mm_P10.16mm_Horizontal";1;"100K";;;
11;"R5,R4";"R_Axial_DIN0207_L6.3mm_D2.5mm_P10.16mm_Horizontal";2;"4,7K";;;
12;"R6";"R_Axial_DIN0207_L6.3mm_D2.5mm_P10.16mm_Horizontal";1;"1,1k";;;
13;"U1";"DIP-16_W7.62mm_Socket_LongPads";1;"TDA8702";;;
14;"X1";"Crystal_HC18-U_Horizontal";1;"10MHz";;;
15;"R7";"R_Axial_DIN0207_L6.3mm_D2.5mm_P10.16mm_Horizontal";1;"1,1K";;;
16;"D3,D2";"LED_D5.0mm";2;"LED";;;
17;"U6";"DIP-8_W7.62mm_LongPads";1;"LM318N";;;
18;"J1";"DSUB-25_Female_Horizontal_P2.77x2.84mm_EdgePinOffset9.90mm_Housed_MountingHolesOffset11.32mm";1;"DB25";;;
19;"U3";"TO-220-3_Horizontal_TabDown";1;"LM7805";;;
20;"J2";"DSUB-9_Female_Horizontal_P2.77x2.84mm_EdgePinOffset4.94mm_Housed_MountingHolesOffset7.48mm";1;"DB9FEM";;;
21;"P2";"TerminalBlock_Phoenix_MKDS-1,5-3-5.08_1x03_P5.08mm_Horizontal";1;"CONN_3";;;
22;"P3";"TerminalBlock_Phoenix_MKDS-1,5-2-5.08_1x02_P5.08mm_Horizontal";1;"CONN_2";;;
23;"C13,C3,C2,C14";"CP_Axial_L10.0mm_D4.5mm_P15.00mm_Horizontal";4;"10uF";;;
24;"C6";"CP_Axial_L10.0mm_D4.5mm_P15.00mm_Horizontal";1;"47uF";;;
25;"U5";"DIP-28__300__600_ELL";1;"RAM_32KO";;;
26;"C1,C12";"C_1206";2;"100nF";;;
27;"C4,C5";"C_1206";2;"22pF";;;
28;"C11,C10,C8,C7";"C_1206_3216Metric_Pad1.24x1.80mm_HandSolder";4;"100nF";;;
